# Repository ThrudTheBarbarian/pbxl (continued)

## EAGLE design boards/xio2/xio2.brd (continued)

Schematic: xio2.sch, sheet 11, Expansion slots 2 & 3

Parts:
C55, C56: 0.1uF; C0201
R63, R64: 10K; R0201
SLOT2, SLOT3: PCIE_64; PCI-E_64

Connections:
+3V3: SLOT2.A2, SLOT2.B5, SLOT2.B6, SLOT2.B7, SLOT3.A2, SLOT3.A3, SLOT3.B5, SLOT3.B6, SLOT3.B7; also elsewhere on the board
+5V: C55.1, C56.1, SLOT2.B1, SLOT2.B2, SLOT2.B3, SLOT3.B1, SLOT3.B2, SLOT3.B3; also elsewhere on the board
GND: C55.2, C56.2, R63.1, R64.1, SLOT2.A1, SLOT2.A3, SLOT2.A4, SLOT2.A5, SLOT2.A6, SLOT2.A7, SLOT3.A1, SLOT3.A4, SLOT3.A5, SLOT3.A6, SLOT3.A7; also elsewhere on the board
HOST_!EXTSEL!: SLOT2.B26, SLOT3.B26; also elsewhere on the board
HOST_!HALT!: SLOT2.B27, SLOT3.B27; also elsewhere on the board
HOST_!IRQ!: SLOT2.B28, SLOT3.B28; also elsewhere on the board
HOST_!MPD!: SLOT2.B29, SLOT3.B29; also elsewhere on the board
HOST_!REF!: SLOT2.B30, SLOT3.B30; also elsewhere on the board
HOST_!RST!: SLOT2.B31, SLOT3.B31; also elsewhere on the board
HOST_A0: SLOT2.A8, SLOT3.A8; also elsewhere on the board
HOST_A1: SLOT2.A9, SLOT3.A9; also elsewhere on the board
HOST_A2: SLOT2.A10, SLOT3.A10; also elsewhere on the board
HOST_A3: SLOT2.A11, SLOT3.A11; also elsewhere on the board
HOST_A4: SLOT2.A12, SLOT3.A12; also elsewhere on the board
HOST_A5: SLOT2.A13, SLOT3.A13; also elsewhere on the board
HOST_A6: SLOT2.A14, SLOT3.A14; also elsewhere on the board
HOST_A7: SLOT2.A15, SLOT3.A15; also elsewhere on the board
HOST_A8: SLOT2.A16, SLOT3.A16; also elsewhere on the board
HOST_A9: SLOT2.A17, SLOT3.A17; also elsewhere on the board
HOST_A10: SLOT2.A18, SLOT3.A18; also elsewhere on the board
HOST_A11: SLOT2.A19, SLOT3.A19; also elsewhere on the board
HOST_A12: SLOT2.A20, SLOT3.A20; also elsewhere on the board
HOST_A13: SLOT2.A21, SLOT3.A21; also elsewhere on the board
HOST_A14: SLOT2.A22, SLOT3.A22; also elsewhere on the board
HOST_A15: SLOT2.A23, SLOT3.A23; also elsewhere on the board
HOST_CLK: SLOT2.A24, SLOT3.A24; also elsewhere on the board
HOST_D0: SLOT2.A25, SLOT3.A25; also elsewhere on the board
HOST_D1: SLOT2.A26, SLOT3.A26; also elsewhere on the board
HOST_D2: SLOT2.A27, SLOT3.A27; also elsewhere on the board
HOST_D3: SLOT2.A28, SLOT3.A28; also elsewhere on the board
HOST_D4: SLOT2.A29, SLOT3.A29; also elsewhere on the board
HOST_D5: SLOT2.A30, SLOT3.A30; also elsewhere on the board
HOST_D6: SLOT2.A31, SLOT3.A31; also elsewhere on the board
HOST_D7: SLOT2.A32, SLOT3.A32; also elsewhere on the board
HOST_R/!W!: SLOT2.B32, SLOT3.B32; also elsewhere on the board
S2_PRESENT: R63.2, SLOT2.B4; also elsewhere on the board
S3_PRESENT: R64.2, SLOT3.B4; also elsewhere on the board
SBUS34_CTL0: SLOT2.B8, SLOT3.B8
SBUS34_CTL1: SLOT2.B9, SLOT3.B9
SBUS34_CTL2: SLOT2.B10, SLOT3.B10
SBUS34_CTL3: SLOT2.B11, SLOT3.B11
SBUS34_CTL4: SLOT2.B12, SLOT3.B12
SBUS34_D0: SLOT2.B18, SLOT3.B18
SBUS34_D1: SLOT2.B19, SLOT3.B19
SBUS34_D2: SLOT2.B20, SLOT3.B20
SBUS34_D3: SLOT2.B21, SLOT3.B21
SBUS34_D4: SLOT2.B22, SLOT3.B22
SBUS34_D5: SLOT2.B23, SLOT3.B23
SBUS34_D6: SLOT2.B24, SLOT3.B24
SBUS34_D7: SLOT2.B25, SLOT3.B25
SPI_CLK: SLOT2.B17, SLOT3.B17; also elsewhere on the board
SPI_IRQ2: SLOT2.B14; also elsewhere on the board
SPI_IRQ3: SLOT3.B14; also elsewhere on the board
SPI_MISO: SLOT2.B16, SLOT3.B16; also elsewhere on the board
SPI_MOSI: SLOT2.B15, SLOT3.B15; also elsewhere on the board
SPI_SS2: SLOT2.B13; also elsewhere on the board
SPI_SS3: SLOT3.B13; also elsewhere on the board

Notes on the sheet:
Slots 2,3
Slot id: 0,1,0
Slot id: 0,1,1
B1,2,3 B5,6,7 B4 A1,2,3 A4,5,6,7
+5V Slot 3.3v Card-present Slot ID GND

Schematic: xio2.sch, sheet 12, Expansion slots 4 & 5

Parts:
C81: 0.1uF; C0201
R65: 10K; R0201
SLOT4: PCIE_64; PCI-E_64

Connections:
+3V3: SLOT4.A1, SLOT4.B5, SLOT4.B6, SLOT4.B7; also elsewhere on the board
+5V: C81.1, SLOT4.B1, SLOT4.B2, SLOT4.B3; also elsewhere on the board
GND: C81.2, R65.1, SLOT4.A2, SLOT4.A3, SLOT4.A4, SLOT4.A5, SLOT4.A6, SLOT4.B8, SLOT4.B9, SLOT4.B10, SLOT4.B11, SLOT4.B12, SLOT4.B18, SLOT4.B19, SLOT4.B20, SLOT4.B21, SLOT4.B22, SLOT4.B23, SLOT4.B24, SLOT4.B25; also elsewhere on the board
HOST_!EXTSEL!: SLOT4.B26; also elsewhere on the board
HOST_!HALT!: SLOT4.B27; also elsewhere on the board
HOST_!IRQ!: SLOT4.B28; also elsewhere on the board
HOST_!MPD!: SLOT4.B29; also elsewhere on the board
HOST_!REF!: SLOT4.B30; also elsewhere on the board
HOST_!RST!: SLOT4.B31; also elsewhere on the board
HOST_A0: SLOT4.A7; also elsewhere on the board
HOST_A1: SLOT4.A8; also elsewhere on the board
HOST_A2: SLOT4.A9; also elsewhere on the board
HOST_A3: SLOT4.A10; also elsewhere on the board
HOST_A4: SLOT4.A11; also elsewhere on the board
HOST_A5: SLOT4.A12; also elsewhere on the board
HOST_A6: SLOT4.A13; also elsewhere on the board
HOST_A7: SLOT4.A14; also elsewhere on the board
HOST_A8: SLOT4.A15; also elsewhere on the board
HOST_A9: SLOT4.A16; also elsewhere on the board
HOST_A10: SLOT4.A17; also elsewhere on the board
HOST_A11: SLOT4.A18; also elsewhere on the board
HOST_A12: SLOT4.A19; also elsewhere on the board
HOST_A13: SLOT4.A20; also elsewhere on the board
HOST_A14: SLOT4.A21; also elsewhere on the board
HOST_A15: SLOT4.A22; also elsewhere on the board
HOST_CLK: SLOT4.A23; also elsewhere on the board
HOST_D0: SLOT4.A24; also elsewhere on the board
HOST_D1: SLOT4.A25; also elsewhere on the board
HOST_D2: SLOT4.A26; also elsewhere on the board
HOST_D3: SLOT4.A27; also elsewhere on the board
HOST_D4: SLOT4.A28; also elsewhere on the board
HOST_D5: SLOT4.A29; also elsewhere on the board
HOST_D6: SLOT4.A30; also elsewhere on the board
HOST_D7: SLOT4.A31; also elsewhere on the board
HOST_R/!W!: SLOT4.B32; also elsewhere on the board
S4_PRESENT: R65.2, SLOT4.B4; also elsewhere on the board
SPI_CLK: SLOT4.B17; also elsewhere on the board
SPI_IRQ4: SLOT4.B14; also elsewhere on the board
SPI_MISO: SLOT4.B16; also elsewhere on the board
SPI_MOSI: SLOT4.B15; also elsewhere on the board
SPI_SS4: SLOT4.B13; also elsewhere on the board

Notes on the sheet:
Slot 4
Slot id: 1,0,0
B1,2,3 B5,6,7 B4 A1,2,3 A4,5,6,7
+5V Slot 3.3v Card-present Slot ID GND

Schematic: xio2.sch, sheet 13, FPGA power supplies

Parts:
C11, C139, C140, C141: 10uF; C0805
C12: 22uF; C2012
C109, C110: 22uF; C0805
C111: 0.01uF; C0402
C112: 3900pF; C0402
C142: 0.1uF; C0402
C143: 1.2nF; C0603
C144: 13pF; C0805
C145: 560pF; C0402
C146: 33uF; C0805
FPGA_1_0: TLV62095; QFN50P310X310X100-16
L1: 1.5uH; L5650M
L2: 2.2uH; RESC4137X200
L3: 470nH; L0603
PEXT_10, PEXT_18: PINHD-1X2; 1X02
PEXT_33: PINHD-2X2; 2X02
R56: 1M; R0402
R129: 499K; R0402
R130: 40.2K; R0402
R131: 160K; R0402
R133: 10.5R; R0402
R134: 48.7K; R0402
R135: 6.04K; R0805
R136: 12K; R0805
R137: 2.67K; R0402
R138: 64.9R; R0402
R139: 105K; R0201
VREG_18: TPS62087RLTR; RLT0007A
VREG_33: LM21212; HTSSOP20

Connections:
+3V3: C145.1, C146.1, L2.2, PEXT_33.1, PEXT_33.2, PEXT_33.3, PEXT_33.4, R136.1; also elsewhere on the board
+5V: C11.1, C109.1, C139.1, C140.1, C141.1, FPGA_1_0.3 (DEF), FPGA_1_0.10 (AVIN), FPGA_1_0.11 (PVIN), FPGA_1_0.12 (PVIN), FPGA_1_0.13 (EN), R56.2, R129.1, R133.2, R139.1, VREG_18.7 (VIN), VREG_33.5 (PVIN), VREG_33.6 (PVIN), VREG_33.7 (PVIN); also elsewhere on the board
GND: C11.2, C12.2, C109.2, C110.2, C112.2, C139.2, C140.2, C141.2, C142.2, C146.2, FPGA_1_0.6 (AGND), FPGA_1_0.14 (PGND), FPGA_1_0.15 (PGND), FPGA_1_0.PAD (AGND), R131.2, R134.1, R137.2, VREG_18.5 (GND), VREG_33.8 (PGND), VREG_33.9 (PGND), VREG_33.10 (PGND), VREG_33.20 (AGND), VREG_33.TAB (GND); also elsewhere on the board
unnamed: L3.1, VREG_18.6 (SW)
unnamed: C111.1, FPGA_1_0.7 (CP)
unnamed: C111.2, FPGA_1_0.8 (CN)
unnamed: FPGA_1_0.1 (SW), FPGA_1_0.2 (SW), L1.1
unnamed: C142.1, R133.1, VREG_33.4 (AVIN)
unnamed: FPGA_1_0.5 (FB), R130.2, R131.1
unnamed: R134.2, VREG_33.1 (FADJ)
unnamed: C112.1, FPGA_1_0.9 (SS)
unnamed: C143.1, C144.1, VREG_33.18 (COMP)
unnamed: C143.2, R135.2
unnamed: C144.2, R135.1, R136.2, R137.1, R138.2, VREG_33.19 (FB)
unnamed: C145.2, R138.1
PGOOD33: R139.2, VREG_33.17 (PGOOD)
PGOOD_10: FPGA_1_0.4 (PG), R129.2, VREG_18.1 (EN)
PGOOD_18: R56.1, VREG_18.2 (PG), VREG_33.3 (EN)
SW_OUT: L2.1, VREG_33.11 (SW), VREG_33.12 (SW), VREG_33.13 (SW), VREG_33.14 (SW), VREG_33.15 (SW), VREG_33.16 (SW)
VCCAUX: C12.1, L3.2, PEXT_18.1, PEXT_18.2, VREG_18.3 (NC), VREG_18.4 (VOS); also elsewhere on the board
VCCINT: C110.1, FPGA_1_0.16 (VOS), L1.2, PEXT_10.1, PEXT_10.2, R130.1; also elsewhere on the board

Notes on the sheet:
C139 C140 C141 C142 C143 C144 C145 C146 R133 R134 R135 R136 R137 R138 R139 L2
Recommended Parts
C11 C12 L3 R56
FPGA power supplies
VCCINT @ 1.0v
Power supply notes
Power sequence is 1.0v rail @ 2A, which enables the 1.8v rail @ 1A, which enables the 3.3v rail @ 1A Both 1.8v and 3.3v need no minimum load All regulators are stable with ceramic caps
R131 and R130 ought to be at least 1%, preferably 0.1% resistors
VCCAUX @ 1.8v
VCCIO @ 3.3v

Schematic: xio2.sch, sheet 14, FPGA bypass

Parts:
C30, C36, C47, C48, C49, C50, C51, C58, C83, C84, C85, C86, C104: 0.47uF; C0201
C52: 47uF; C0805
C59, C74, C75, C76, C78, C79, C82, C102: 4.7uF; C0402
C73, C77, C101: 100uF; C0805
XC7S25: XC7S25; BGA196C100P14X14_1500X1500X146

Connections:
+3V3: C47.1, C48.1, C49.1, C50.1, C76.1, C77.1, C78.1, C79.1, C82.1, C83.1, C84.1, C85.1, C86.1; also elsewhere on the board
GND: C30.2, C36.2, C47.2, C48.2, C49.2, C50.2, C51.2, C52.2, C58.2, C59.2, C73.2, C74.2, C75.2, C76.2, C77.2, C78.2, C79.2, C82.2, C83.2, C84.2, C85.2, C86.2, C101.2, C102.2, C104.2, XC7S25.A1 (GND), XC7S25.A6 (GND), XC7S25.A9 (GND), XC7S25.A11 (GND), XC7S25.A14 (GND), XC7S25.B4 (GND), XC7S25.B7 (GND), XC7S25.B9 (GND), XC7S25.C2 (GND), XC7S25.C6 (GND), XC7S25.C7 (GND), XC7S25.C8 (GND), XC7S25.C9 (GND), XC7S25.C13 (GND), XC7S25.D5 (GND), XC7S25.D7 (GND), XC7S25.D9 (GND), XC7S25.D11 (GND), XC7S25.E1 (GND), XC7S25.E3 (GND), XC7S25.E6 (GND), XC7S25.E8 (GND), XC7S25.E10 (GND), XC7S25.E14 (GND), XC7S25.F5 (GND), XC7S25.F7 (GND_ADC_0), XC7S25.F9 (GND), XC7S25.G3 (GND), XC7S25.G6 (GND), XC7S25.G8 (VP_0), XC7S25.G10 (GND), XC7S25.G12 (GND), XC7S25.H5 (GND), XC7S25.H7 (VN_0), XC7S25.H9 (GND), XC7S25.J6 (GND), XC7S25.J10 (GND), XC7S25.K1 (GND), XC7S25.K5 (GND), XC7S25.K7 (GND), XC7S25.K9 (GND), XC7S25.K14 (GND), XC7S25.L4 (GND), XC7S25.L6 (GND), XC7S25.L8 (GND), XC7S25.L10 (GND), XC7S25.L11 (GND), XC7S25.N3 (GND), XC7S25.N5 (GND), XC7S25.N9 (GND), XC7S25.N12 (GND), XC7S25.P1 (GND), XC7S25.P14 (GND); also elsewhere on the board
VCCAUX: C51.1, C52.1, C58.1, C59.1, XC7S25.F8 (VCC_ADC_0), XC7S25.F10 (VCCAUX), XC7S25.H10 (VCCAUX), XC7S25.K10 (VCCAUX), XC7S25.L9 (VCCAUX); also elsewhere on the board
VCCINT: C30.1, C36.1, C73.1, C74.1, C75.1, C101.1, C102.1, C104.1, XC7S25.D6 (VCCINT), XC7S25.D8 (VCCINT), XC7S25.E5 (VCCBRAM), XC7S25.E7 (VCCINT), XC7S25.E9 (VCCINT), XC7S25.F6 (VCCINT), XC7S25.G5 (VCCBRAM), XC7S25.G9 (VCCINT), XC7S25.H6 (VCCINT), XC7S25.J5 (VCCBRAM), XC7S25.J9 (VCCINT), XC7S25.K6 (VCCINT), XC7S25.K8 (VCCINT); also elsewhere on the board

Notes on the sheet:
VccAux bypass caps
VccInt bypass caps
VccO bank 14
Bypass cap number and capacitance taken from UG483
VccBram bypass caps
VccO bank 34
No need for second 100uF
100uF 47uF 4.7uF 0.47uF
: GRM21BR60J107ME15L (0805) : GRM21BR60J476ME15L (0805) : GRM155R60J475ME87D (0402) : GRM033R60J474KE90D (0201)
100uF caps can be placed anywhere others within 2 electrical inches of part
FPGA power
Xilinx-recommended (smaller parts)
XADC is not used

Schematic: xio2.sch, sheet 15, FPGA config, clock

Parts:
A_MUX: TS3A27518EPWR; TSSOP24
BOOT_MODE: 209-3MS; EDG-03
C25, C96: 0.1uF; C0201
C97: 1uF; C0201
FPGA_CFG: W25Q80DVSNIG; SOIC8_150MIL
FPGA_DONE: LTST-C191KFKT; CHIPLED_0603
FPGA_PROG: XILINX-JTAG; 332-14
R52, R60: 33R; R0201
R54, R55, R57: 2.4K; R0201
R66: 200R; R0201
R68: 100R; R0402
R69, R70, R71, R78, R79: 4.7K; R0201
R82, R83, R84, R85: 10K; R0201
R125, R126, R127: 47K; R0201
R128: 1K; R0201
RESET_S7: Tac-switch; TACTILE-PTH
XC7S25: XC7S25; BGA196C100P14X14_1500X1500X146

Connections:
+3V3: A_MUX.8 (VCC), A_MUX.16 (NO6), A_MUX.18 (NO5), C25.1, C96.1, C97.1, FPGA_CFG.8 (VCC), FPGA_PROG.2 (VREF), R54.2, R55.2, R57.2, R66.2, R69.2, R78.2, R79.2, R82.1, R83.1, R84.1, R85.1, R128.1, XC7S25.N6 (VCCO_0), XC7S25.N8 (VCCO_0); also elsewhere on the board
BOOT_M0: BOOT_MODE.1, R127.1, XC7S25.M7 (M0_0)
BOOT_M1: BOOT_MODE.2, R126.1, XC7S25.M8 (M1_0)
BOOT_M2: BOOT_MODE.3, R125.1, XC7S25.M9 (M2_0)
FLASH_CLK: A_MUX.2 (NC1), R52.2
FLASH_CS: A_MUX.21 (NC4), R57.1, XC7S25.C11 (IO_L6P_T0_FCS_B_14)
FLASH_D0: A_MUX.1 (NC2), R60.2
FLASH_D1: A_MUX.23 (NC3), XC7S25.B12 (IO_L1N_T0_D01_DIN_14)
FLASH_D2: A_MUX.19 (NC5), R55.1, XC7S25.D10 (IO_L2P_T0_D02_14)
FLASH_D3: A_MUX.22 (NC6), R54.1, XC7S25.C10 (IO_L2N_T0_D03_14)
GND: A_MUX.5 (GND), A_MUX.17 (NO4), C25.2, C96.2, C97.2, FPGA_CFG.4 (VSS), FPGA_DONE.C, FPGA_PROG.1 (GND), FPGA_PROG.3 (GND), FPGA_PROG.5 (GND), FPGA_PROG.7 (GND), FPGA_PROG.9 (GND), FPGA_PROG.11 (GND), FPGA_PROG.13 (GND), R70.2, R71.2, R125.2, R126.2, R127.2, RESET_S7.1, RESET_S7.2, XC7S25.J7 (DXN_0), XC7S25.J8 (DXP_0); also elsewhere on the board
unnamed: R60.1, XC7S25.B11 (IO_L1P_T0_D00_MOSI_14)
unnamed: A_MUX.4 (COM1), FPGA_CFG.6 (SCK)
unnamed: BOOT_MODE.4, BOOT_MODE.5, BOOT_MODE.6, R128.2
unnamed: R52.1, XC7S25.A8 (CCLK_0)
unnamed: R66.1, R68.2, XC7S25.P9 (DONE_0)
unnamed: FPGA_DONE.A, R68.1
unnamed: A_MUX.6 (COM2), FPGA_CFG.5 (MOSI)
unnamed: A_MUX.7 (COM3), FPGA_CFG.2 (MISO)
unnamed: A_MUX.9 (COM4), FPGA_CFG.1 (SSEL)
unnamed: A_MUX.10 (COM5), FPGA_CFG.3 (#WP/IO2)
unnamed: A_MUX.12 (COM6), FPGA_CFG.7 (#HOLD/IO3)
unnamed: R69.1, RESET_S7.3, RESET_S7.4, XC7S25.L7 (PROGRAM_B_0)
unnamed: R78.1, XC7S25.P8 (INIT_B_0)
unnamed: A_MUX.20 (!EN!), R70.1
unnamed: R79.1, XC7S25.N7 (CFGBVS_0)
SPI_CLK: A_MUX.11 (NO1); also elsewhere on the board
SPI_MISO: A_MUX.15 (NO3); also elsewhere on the board
SPI_MOSI: A_MUX.13 (NO2); also elsewhere on the board
SPI_MUX_IN: A_MUX.14 (IN2), A_MUX.24 (IN1), R71.1; also elsewhere on the board
TCK: FPGA_PROG.6 (SCK/CCLK/TCK), R83.2, XC7S25.A7 (TCK_0)
TDI: FPGA_PROG.10 (MOSI/DIN/TDI), R85.2, XC7S25.P7 (TDI_0)
TDO: FPGA_PROG.8 (MISO/DONE/TDO), R84.2, XC7S25.P6 (TDO_0)
TMS: FPGA_PROG.4 (SS/PROG/TMS), R82.2, XC7S25.M6 (TMS_0)
VCCAUX: XC7S25.B8 (VCC_BATT_0); also elsewhere on the board

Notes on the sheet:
Bank 0 / Flash Config
Trace thickness Prepreg thickness Trace width Prepreg dielectric Trace impedance
0.035 mm 0.12 mm 8 mil 4.4 50.2 ohms
FLASH_CLK impedance matching
Default (NC) is that the FPGA has control over the SPI flash. If the STM pulls SPI_MUX_IN high, it gains control
Pins 12,14 are NC
Temp Sense Diodes Not Used
Done goes high once configuration completes
MUX operation
Boot mode
JTAG mode: Set M[2:0] to 101 Master SPI : Set M[2:0] to 001
Pull-ups for the JTAG lines

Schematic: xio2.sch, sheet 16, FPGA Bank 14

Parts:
HOST_IO: PINHD-2X20/90; 2X20/90
J1: 12401598E4#2A; AMPHENOL_12401598E4#2A
R59, R81: 10K; R0201
R113, R114, R115, R116, R117, R118: 50R; R0201
XC7S25: XC7S25; BGA196C100P14X14_1500X1500X146

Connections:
+3V3: R59.1, R113.2, R114.2, R115.2, R116.2, R117.2, R118.2, XC7S25.G13 (VCCO_14), XC7S25.K13 (VCCO_14), XC7S25.N13 (VCCO_14); also elsewhere on the board
GND: HOST_IO.40, J1.A1 (GND), J1.A12 (GND), J1.B1 (GND), J1.B12 (GND), J1.SH1 (SHIELD), J1.SH2 (SHIELD), J1.SH3 (SHIELD), J1.SH4 (SHIELD), R81.2; also elsewhere on the board
HOST_!EXTSEL!: HOST_IO.35, XC7S25.J11 (IO_L17P_T2_D30_14); also elsewhere on the board
HOST_!HALT!: HOST_IO.37, XC7S25.J12 (IO_L17N_T2_D29_14); also elsewhere on the board
HOST_!IRQ!: HOST_IO.39, XC7S25.K11 (IO_L19P_T3_D26_14); also elsewhere on the board
HOST_!MPD!: HOST_IO.32, XC7S25.K12 (IO_L19N_T3_D25_VREF_14); also elsewhere on the board
HOST_!REF!: HOST_IO.34, XC7S25.M11 (IO_L20P_T3_D24_14); also elsewhere on the board
HOST_!RST!: HOST_IO.36, XC7S25.M12 (IO_L20N_T3_D23_14); also elsewhere on the board
HOST_A0: HOST_IO.1, R59.2, R81.1, XC7S25.B10 (IO_L3P_T0_DQS_PUDC_B_14); also elsewhere on the board
HOST_A1: HOST_IO.3, XC7S25.A10 (IO_L3N_T0_DQS_EMCCLK_14); also elsewhere on the board
HOST_A2: HOST_IO.5, XC7S25.A12 (IO_L4P_T0_D04_14); also elsewhere on the board
HOST_A3: HOST_IO.7, XC7S25.A13 (IO_L4N_T0_D05_14); also elsewhere on the board
HOST_A4: HOST_IO.9, XC7S25.B13 (IO_L5P_T0_D06_14); also elsewhere on the board
HOST_A5: HOST_IO.11, XC7S25.B14 (IO_L5N_T0_D07_14); also elsewhere on the board
HOST_A6: HOST_IO.13, XC7S25.C12 (IO_L6N_T0_D08_VREF_14); also elsewhere on the board
HOST_A7: HOST_IO.15, XC7S25.F12 (IO_L7P_T1_D09_14); also elsewhere on the board
HOST_A8: HOST_IO.17, XC7S25.E12 (IO_L7N_T1_D10_14); also elsewhere on the board
HOST_A9: HOST_IO.19, XC7S25.D12 (IO_L8P_T1_D11_14); also elsewhere on the board
HOST_A10: HOST_IO.21, XC7S25.D13 (IO_L8N_T1_D12_14); also elsewhere on the board
HOST_A11: HOST_IO.23, XC7S25.G14 (IO_L9P_T1_DQS_14); also elsewhere on the board
HOST_A12: HOST_IO.25, XC7S25.F14 (IO_L9N_T1_DQS_D13_14); also elsewhere on the board
HOST_A13: HOST_IO.27, XC7S25.F13 (IO_L10P_T1_D14_14); also elsewhere on the board
HOST_A14: HOST_IO.29, XC7S25.E13 (IO_L10N_T1_D15_14); also elsewhere on the board
HOST_A15: HOST_IO.31, XC7S25.D14 (IO_L11P_T1_SRCC_14); also elsewhere on the board
HOST_CLK: HOST_IO.33, XC7S25.E11 (IO_0_14); also elsewhere on the board
HOST_CTL0: HOST_IO.2, XC7S25.N10 (IO_L23P_T3_D19_14)
HOST_CTL1: HOST_IO.4, XC7S25.N11 (IO_L23N_T3_D18_14)
HOST_D0: HOST_IO.6, XC7S25.C14 (IO_L11N_T1_SRCC_14); also elsewhere on the board
HOST_D1: HOST_IO.8, XC7S25.G11 (IO_L12P_T1_MRCC_14); also elsewhere on the board
HOST_D2: HOST_IO.10, XC7S25.F11 (IO_L12N_T1_MRCC_14); also elsewhere on the board
HOST_D3: HOST_IO.12, XC7S25.H11 (IO_L13P_T2_MRCC_14); also elsewhere on the board
HOST_D4: HOST_IO.14, XC7S25.H12 (IO_L13N_T2_MRCC_14); also elsewhere on the board
HOST_D5: HOST_IO.16, XC7S25.M13 (IO_L15P_T2_DQS_RDWR_B_14); also elsewhere on the board
HOST_D6: HOST_IO.18, XC7S25.L12 (IO_L16P_T2_CSI_B_14); also elsewhere on the board
HOST_D7: HOST_IO.20, XC7S25.L13 (IO_L16N_T2_D31_14); also elsewhere on the board
HOST_DIR0: HOST_IO.22; also elsewhere on the board
HOST_DIR1: HOST_IO.24; also elsewhere on the board
HOST_DIR2: HOST_IO.26; also elsewhere on the board
HOST_DIR3: HOST_IO.28; also elsewhere on the board
HOST_DIR4: HOST_IO.30; also elsewhere on the board
HOST_R/!W!: HOST_IO.38, XC7S25.L14 (IO_L15N_T2_DQS_DOUT_CSO_B_14); also elsewhere on the board
LX_MISC: J1.A5 (CC1), XC7S25.M10 (IO_25_14)
LX_RC_N: J1.B11 (SSRXP1), XC7S25.P11 (IO_L24N_T3_D16_14)
LX_RC_P: J1.B10 (SSRXN1), XC7S25.P10 (IO_L24P_T3_D17_14)
LX_RD_N: J1.B2 (SSTXP2), XC7S25.H14 (IO_L14N_T2_SRCC_14)
LX_RD_P: J1.B3 (SSTXN2), XC7S25.H13 (IO_L14P_T2_SRCC_14)
LX_TC_N: J1.A7 (DN1), R113.1, XC7S25.M14 (IO_L21N_T3_DQS_D22_14)
LX_TC_P: J1.A6 (DP1), R114.1, XC7S25.N14 (IO_L21P_T3_DQS_14)
LX_TD0_N: J1.A3 (SSTXN1), R115.1, XC7S25.P13 (IO_L22N_T3_D20_14)
LX_TD0_P: J1.A2 (SSTXP1), R116.1, XC7S25.P12 (IO_L22P_T3_D21_14)
LX_TD1_N: J1.A10 (SSRXN2), R117.1, XC7S25.J14 (IO_L18N_T2_D27_14)
LX_TD1_P: J1.A11 (SSRXP2), R118.1, XC7S25.J13 (IO_L18P_T2_D28_14)

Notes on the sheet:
Trace thickness Prepreg thickness Trace width Inter-trace spacing Prepreg dielectric Differential impedance
0.035 mm 0.12 mm 10 mil 7 mil 4.4 90.5 ohms
USB3 connections
FPGA Bank 14
TMDS_33 signalling requires 50R pull-ups to 3.3v on all inputs. Labels {RX*,TX*} are from perspective of the host board, so need to add pull-ups to TX* lines on this board. Will dissipate 13.5mA,
Pull-up specification
PUDC (connected to HOST_A0) cannot be floating according to UG470 (p27). The host interface can drive plenty to overpower a 10k pull-up and it's a slow bus, so this ought to work ok.
PUDC control

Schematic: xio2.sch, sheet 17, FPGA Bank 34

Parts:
C35, C88, C100: 0.1uF; C0201
EXPANSION: PINHD-2X6; 2X06
EXP_POWER: PINHD-1X2; 1X02
MUX-HI: IDTQS3VH257; SO16
MUX-LO: IDTQS3VH257; SO16
OSC1: 50 MHz oscillator; OSC_3.2X2.5MM
R58: 1K; R0201
R73, R74, R75: 33R; R0201
XC7S25: XC7S25; BGA196C100P14X14_1500X1500X146

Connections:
!ADDR_VALID_READ!: XC7S25.D1 (IO_L11P_T1_SRCC_34); also elsewhere on the board
!ADDR_VALID_WRITE!: XC7S25.C1 (IO_L11N_T1_SRCC_34); also elsewhere on the board
!GEN_CCTL!: XC7S25.F4 (IO_L12N_T1_MRCC_34); also elsewhere on the board
!GEN_S4!: XC7S25.H3 (IO_L13N_T2_MRCC_34); also elsewhere on the board
!GEN_S5!: XC7S25.H2 (IO_L14P_T2_SRCC_34); also elsewhere on the board
!SPI_IRQ!: XC7S25.L2 (IO_L22N_T3_34); also elsewhere on the board
+3V3: C35.1, C88.1, C100.1, EXPANSION.1, EXP_POWER.1, MUX-HI.16 (VCC), MUX-LO.16 (VCC), OSC1.4 (VCC), R58.1, XC7S25.G2 (VCCO_34), XC7S25.K2 (VCCO_34), XC7S25.N2 (VCCO_34); also elsewhere on the board
CART_RD4: XC7S25.H1 (IO_L14N_T2_SRCC_34); also elsewhere on the board
CART_RD5: XC7S25.J2 (IO_L15P_T2_DQS_34); also elsewhere on the board
EXT_IO0: EXPANSION.8; also elsewhere on the board
EXT_IO1: EXPANSION.10; also elsewhere on the board
FPGA_EXT0: EXPANSION.2, XC7S25.K3 (IO_L16N_T2_34)
FPGA_EXT1: EXPANSION.3, XC7S25.J4 (IO_L17P_T2_34)
FPGA_EXT2: EXPANSION.4, XC7S25.J3 (IO_L17N_T2_34)
FPGA_EXT3: EXPANSION.5, XC7S25.M1 (IO_L18P_T2_34)
FPGA_EXT4: EXPANSION.6, XC7S25.L1 (IO_L18N_T2_34)
FPGA_EXT5: EXPANSION.7, XC7S25.M3 (IO_L19P_T3_34)
GND: C35.2, C88.2, C100.2, EXPANSION.9, EXPANSION.11, EXPANSION.12, EXP_POWER.2, MUX-HI.8 (GND), MUX-HI.15 (!E!), MUX-LO.8 (GND), MUX-LO.15 (!E!), OSC1.2 (GND); also elsewhere on the board
HOST_DIR0: XC7S25.B6 (IO_0_34); also elsewhere on the board
HOST_DIR1: XC7S25.D3 (IO_L1P_T0_34); also elsewhere on the board
HOST_DIR2: XC7S25.C3 (IO_L1N_T0_34); also elsewhere on the board
HOST_DIR3: XC7S25.A4 (IO_L2P_T0_34); also elsewhere on the board
HOST_DIR4: XC7S25.A3 (IO_L2N_T0_34); also elsewhere on the board
LX_CLK: OSC1.3 (OUT), XC7S25.G4 (IO_L12P_T1_MRCC_34)
unnamed: OSC1.1 (INH), R58.2
S7_DBG0: XC7S25.H4 (IO_L13P_T2_MRCC_34); also elsewhere on the board
S7_DBG1: XC7S25.J1 (IO_L15N_T2_DQS_34); also elsewhere on the board
S7_DBG2: XC7S25.K4 (IO_L16P_T2_34); also elsewhere on the board
SPI_IRQ0: XC7S25.L5 (IO_25_34); also elsewhere on the board
SPI_IRQ1: XC7S25.N4 (IO_L24N_T3_34); also elsewhere on the board
SPI_IRQ2: XC7S25.P5 (IO_L24P_T3_34); also elsewhere on the board
SPI_IRQ3: XC7S25.M4 (IO_L23N_T3_34); also elsewhere on the board
SPI_IRQ4: XC7S25.M5 (IO_L23P_T3_34); also elsewhere on the board
STMDATA_A0: MUX-LO.2 (A0), XC7S25.B3 (IO_L3P_T0_DQS_34)
STMDATA_A1: MUX-LO.5 (A1), XC7S25.A2 (IO_L3N_T0_DQS_34)
STMDATA_A2: MUX-LO.11 (A2), XC7S25.B5 (IO_L4P_T0_34)
STMDATA_A3: MUX-LO.14 (A3), XC7S25.A5 (IO_L4N_T0_34)
STMDATA_A4: MUX-HI.2 (A0), XC7S25.B2 (IO_L5P_T0_34)
STMDATA_A5: MUX-HI.5 (A1), XC7S25.B1 (IO_L5N_T0_34)
STMDATA_A6: MUX-HI.11 (A2), XC7S25.C5 (IO_L6P_T0_34)
STMDATA_A7: MUX-HI.14 (A3), XC7S25.C4 (IO_L6N_T0_VREF_34)
STMDATA_B0: MUX-LO.3 (B0), XC7S25.E4 (IO_L7P_T1_34)
STMDATA_B1: MUX-LO.6 (B1), XC7S25.D4 (IO_L7N_T1_34)
STMDATA_B2: MUX-LO.10 (B2), XC7S25.F3 (IO_L8P_T1_34)
STMDATA_B3: MUX-LO.13 (B3), XC7S25.F2 (IO_L8N_T1_34)
STMDATA_B4: MUX-HI.3 (B0), XC7S25.G1 (IO_L9P_T1_DQS_34)
STMDATA_B5: MUX-HI.6 (B1), XC7S25.F1 (IO_L9N_T1_DQS_34)
STMDATA_B6: MUX-HI.10 (B2), XC7S25.E2 (IO_L10P_T1_34)
STMDATA_B7: MUX-HI.13 (B3), XC7S25.D2 (IO_L10N_T1_34)
STM_MUX_CTL: MUX-HI.1 (S), MUX-LO.1 (S); also elsewhere on the board
STM_MUX_D0: MUX-LO.4 (Y0); also elsewhere on the board
STM_MUX_D1: MUX-LO.7 (Y1); also elsewhere on the board
STM_MUX_D2: MUX-LO.9 (Y2); also elsewhere on the board
STM_MUX_D3: MUX-LO.12 (Y3); also elsewhere on the board
STM_MUX_D4: MUX-HI.4 (Y0); also elsewhere on the board
STM_MUX_D5: MUX-HI.7 (Y1); also elsewhere on the board
STM_MUX_D6: MUX-HI.9 (Y2); also elsewhere on the board
STM_MUX_D7: MUX-HI.12 (Y3); also elsewhere on the board
XSPI5_MISO: XC7S25.P3 (IO_L21N_T3_DQS_34); also elsewhere on the board
XSPI5_MOSI: R74.1; also elsewhere on the board
XSPI5_MOSI_R: R74.2, XC7S25.L3 (IO_L22P_T3_34)
XSPI5_SCK: R75.1; also elsewhere on the board
XSPI5_SCK_R: R75.2, XC7S25.P4 (IO_L21P_T3_DQS_34)
XSPI6_MISO: R73.1; also elsewhere on the board
XSPI6_MISO_R: R73.2, XC7S25.P2 (IO_L20P_T3_34)
XSPI6_MOSI: XC7S25.N1 (IO_L20N_T3_34); also elsewhere on the board
XSPI6_SCK: XC7S25.M2 (IO_L19N_T3_VREF_34); also elsewhere on the board

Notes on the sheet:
STMDATA_A* is an input STMDATA_B* is an output STM controls whether to read or write data using STM_MUX_CTL in IRQ handler Mux removes need to sync FPGA & STM
SPI5 to be used with FPGA as master. SPI6 to be used with STM as master Resistors sited close to source signal
SPI termination
HOST_DIR0 : HOST_DIR1 : HOST_DIR2 : HOST_DIR3 : HOST_DIR4 :
Direction control
Host data bus Host address bus Host R/!W! signal Host !REF! signal Host !HALT! signal
STM32 data bus
Bypass caps for muxes
FPGA Bank 34
This is for a more stable board mount

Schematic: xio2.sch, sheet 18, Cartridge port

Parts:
C57, C60, C61, C62, C63, C64, C65, C66, C67, C68, C69, C70, C71, C72: 0.1uF; C0201
CARTRIDGE: 5650118-1; A8_CART
LVL_AHI: SN74LVC8T245; TSSOP24
LVL_ALO: SN74LVC8T245; TSSOP24
LVL_D: SN74LVC8T245; TSSOP24
U$5, U$6, U$7, U$8: 74LVC1T45GWSOT866; SOT886

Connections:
!GEN_CCTL!: LVL_AHI.8 (A6); also elsewhere on the board
!GEN_S4!: LVL_AHI.9 (A7); also elsewhere on the board
!GEN_S5!: LVL_AHI.10 (A8); also elsewhere on the board
+3V3: C57.1, C60.1, C61.1, C62.1, C63.1, C64.1, C65.1, LVL_AHI.1 (VCCA), LVL_AHI.2 (DIR), LVL_ALO.1 (VCCA), LVL_ALO.2 (DIR), LVL_D.1 (VCCA), U$5.1 (VCCA), U$5.5 (DIR), U$6.1 (VCCA), U$6.5 (DIR), U$7.6 (VCCB), U$8.6 (VCCB); also elsewhere on the board
+5V: C66.1, C67.1, C68.1, C69.1, C70.1, C71.1, C72.1, CARTRIDGE.P13 (VCC5), LVL_AHI.23 (VCCB), LVL_AHI.24 (VCCB), LVL_ALO.23 (VCCB), LVL_ALO.24 (VCCB), LVL_D.23 (VCCB), LVL_D.24 (VCCB), U$5.6 (VCCB), U$6.6 (VCCB), U$7.1 (VCCA), U$7.5 (DIR), U$8.1 (VCCA), U$8.5 (DIR); also elsewhere on the board
CART_!CCTL!: CARTRIDGE.P15 (!CCTL!), LVL_AHI.16 (B6)
CART_!S4!: CARTRIDGE.P1 (!S4!), LVL_AHI.15 (B7)
CART_!S5!: CARTRIDGE.P12 (!S5!), LVL_AHI.14 (B8)
CART_A0: CARTRIDGE.P5 (A0), LVL_ALO.21 (B1)
CART_A1: CARTRIDGE.P4 (A1), LVL_ALO.20 (B2)
CART_A2: CARTRIDGE.P3 (A2), LVL_ALO.19 (B3)
CART_A3: CARTRIDGE.P2 (A3), LVL_ALO.18 (B4)
CART_A4: CARTRIDGE.PC (A4), LVL_ALO.17 (B5)
CART_A5: CARTRIDGE.PD (A5), LVL_ALO.16 (B6)
CART_A6: CARTRIDGE.PE (A6), LVL_ALO.15 (B7)
CART_A7: CARTRIDGE.PF (A7), LVL_ALO.14 (B8)
CART_A8: CARTRIDGE.PH (A8), LVL_AHI.21 (B1)
CART_A9: CARTRIDGE.PJ (A9), LVL_AHI.20 (B2)
CART_A10: CARTRIDGE.PP (A10), LVL_AHI.19 (B3)
CART_A11: CARTRIDGE.PN (A11), LVL_AHI.18 (B4)
CART_A12: CARTRIDGE.PK (A12), LVL_AHI.17 (B5)
CART_CLK: CARTRIDGE.PS (B02), U$5.4 (B)
CART_D0: CARTRIDGE.P10 (D0), LVL_D.21 (B1)
CART_D1: CARTRIDGE.P9 (D1), LVL_D.20 (B2)
CART_D2: CARTRIDGE.P8 (D2), LVL_D.19 (B3)
CART_D3: CARTRIDGE.PL (D3), LVL_D.18 (B4)
CART_D4: CARTRIDGE.P6 (D4), LVL_D.17 (B5)
CART_D5: CARTRIDGE.P7 (D5), LVL_D.16 (B6)
CART_D6: CARTRIDGE.P11 (D6), LVL_D.15 (B7)
CART_D7: CARTRIDGE.PM (D7), LVL_D.14 (B8)
CART_R/!W!: CARTRIDGE.PR (R/!W!), U$6.4 (B)
CART_RD4: U$7.4 (B); also elsewhere on the board
CART_RD5: U$8.4 (B); also elsewhere on the board
GND: C57.2, C60.2, C61.2, C62.2, C63.2, C64.2, C65.2, C66.2, C67.2, C68.2, C69.2, C70.2, C71.2, C72.2, CARTRIDGE.PB (GND), LVL_AHI.11 (GND), LVL_AHI.12 (GND), LVL_AHI.13 (GND), LVL_AHI.22 (!OE!), LVL_ALO.11 (GND), LVL_ALO.12 (GND), LVL_ALO.13 (GND), LVL_ALO.22 (!OE!), LVL_D.11 (GND), LVL_D.12 (GND), LVL_D.13 (GND), LVL_D.22 (!OE!), U$5.2 (GND), U$6.2 (GND), U$7.2 (GND), U$8.2 (GND); also elsewhere on the board
HOST_A0: LVL_ALO.3 (A1); also elsewhere on the board
HOST_A1: LVL_ALO.4 (A2); also elsewhere on the board
HOST_A2: LVL_ALO.5 (A3); also elsewhere on the board
HOST_A3: LVL_ALO.6 (A4); also elsewhere on the board
HOST_A4: LVL_ALO.7 (A5); also elsewhere on the board
HOST_A5: LVL_ALO.8 (A6); also elsewhere on the board
HOST_A6: LVL_ALO.9 (A7); also elsewhere on the board
HOST_A7: LVL_ALO.10 (A8); also elsewhere on the board
HOST_A8: LVL_AHI.3 (A1); also elsewhere on the board
HOST_A9: LVL_AHI.4 (A2); also elsewhere on the board
HOST_A10: LVL_AHI.5 (A3); also elsewhere on the board
HOST_A11: LVL_AHI.6 (A4); also elsewhere on the board
HOST_A12: LVL_AHI.7 (A5); also elsewhere on the board
HOST_CLK: U$5.3 (A); also elsewhere on the board
HOST_D0: LVL_D.3 (A1); also elsewhere on the board
HOST_D1: LVL_D.4 (A2); also elsewhere on the board
HOST_D2: LVL_D.5 (A3); also elsewhere on the board
HOST_D3: LVL_D.6 (A4); also elsewhere on the board
HOST_D4: LVL_D.7 (A5); also elsewhere on the board
HOST_D5: LVL_D.8 (A6); also elsewhere on the board
HOST_D6: LVL_D.9 (A7); also elsewhere on the board
HOST_D7: LVL_D.10 (A8); also elsewhere on the board
HOST_DIR0: LVL_D.2 (DIR); also elsewhere on the board
HOST_R/!W!: U$6.3 (A); also elsewhere on the board
unnamed: CARTRIDGE.PA (RD4), U$7.3 (A)
unnamed: CARTRIDGE.P14 (RD5), U$8.3 (A)

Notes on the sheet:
Dir=high : A->B tPD_AB : 0.7 .. 4.4ns tPD_BA : 0.6 .. 5.4ns
74LVCH1T45GW:
SN74LVC8T245:
Dir=high : A->B tPD_AB : 0.5 .. 4.4ns tPD_BA : 0.6 .. 6ns
HOST_DIR0 :
Direction control / timings
Host data bus
Cartridge support

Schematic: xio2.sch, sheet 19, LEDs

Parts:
LD_0ACT, LD_1ACT, LD_2ACT, LD_3ACT, LD_4ACT: LTST-C191KRKT; CHIPLED_0603
LD_0P, LD_1P, LD_2P, LD_3P, LD_4P: SML-D12D1WT86; CHIPLED_0603
LD_7DBG0, LD_7DBG1, LD_7DBG2: IN-S63BTA; CHIPLED_0603
LD_AUX: LTST-S270GKT; CHIPLED_0603
LD_INT: LTST-S270GKT; CHIPLED_0603
LD_V33: LTST-S270GKT; CHIPLED_0603
Q3, Q4: BC817-16LT3G; SOT23-R
R67, R77: 150R; R0402
R76, R80: 330R; R0402
R87, R98, R101, R104, R107, R112: 59R; R0402
R94, R99, R102, R105, R108, R109, R110, R111: 130R; R0402

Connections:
+3V3: R112.1; also elsewhere on the board
+5V: R67.1, R77.1; also elsewhere on the board
GND: LD_0ACT.C, LD_0P.C, LD_1ACT.C, LD_1P.C, LD_2ACT.C, LD_2P.C, LD_3ACT.C, LD_3P.C, LD_4ACT.C, LD_4P.C, LD_7DBG0.C, LD_7DBG1.C, LD_7DBG2.C, LD_V33.C, Q3.2 (E), Q4.2 (E); also elsewhere on the board
unnamed: LD_INT.A, R67.2
unnamed: Q3.1 (B), R76.1
unnamed: LD_INT.C, Q3.3 (C)
unnamed: LD_AUX.A, R77.2
unnamed: LD_0P.A, R87.2
unnamed: LD_0ACT.A, R94.2
unnamed: Q4.1 (B), R80.1
unnamed: LD_AUX.C, Q4.3 (C)
unnamed: LD_1P.A, R98.2
unnamed: LD_1ACT.A, R99.2
unnamed: LD_2P.A, R101.2
unnamed: LD_2ACT.A, R102.2
unnamed: LD_3P.A, R104.2
unnamed: LD_3ACT.A, R105.2
unnamed: LD_4P.A, R107.2
unnamed: LD_4ACT.A, R108.2
unnamed: LD_7DBG0.A, R109.2
unnamed: LD_7DBG1.A, R110.2
unnamed: LD_7DBG2.A, R111.2
unnamed: LD_V33.A, R112.2
S0_PRESENT: R87.1; also elsewhere on the board
S1_PRESENT: R98.1; also elsewhere on the board
S2_PRESENT: R101.1; also elsewhere on the board
S3_PRESENT: R104.1; also elsewhere on the board
S4_PRESENT: R107.1; also elsewhere on the board
S7_DBG0: R109.1; also elsewhere on the board
S7_DBG1: R110.1; also elsewhere on the board
S7_DBG2: R111.1; also elsewhere on the board
SPI_SS0: R94.1; also elsewhere on the board
SPI_SS1: R99.1; also elsewhere on the board
SPI_SS2: R102.1; also elsewhere on the board
SPI_SS3: R105.1; also elsewhere on the board
SPI_SS4: R108.1; also elsewhere on the board
VCCAUX: R80.2; also elsewhere on the board
VCCINT: R76.2; also elsewhere on the board

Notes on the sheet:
Debugging LEDs
Green LED
Amber LED
Orange LED
Red LED
Green and Orange LEDs are configured for 20mA current
Amber and Red LEDs are configured for 10mA current
LED resistor values

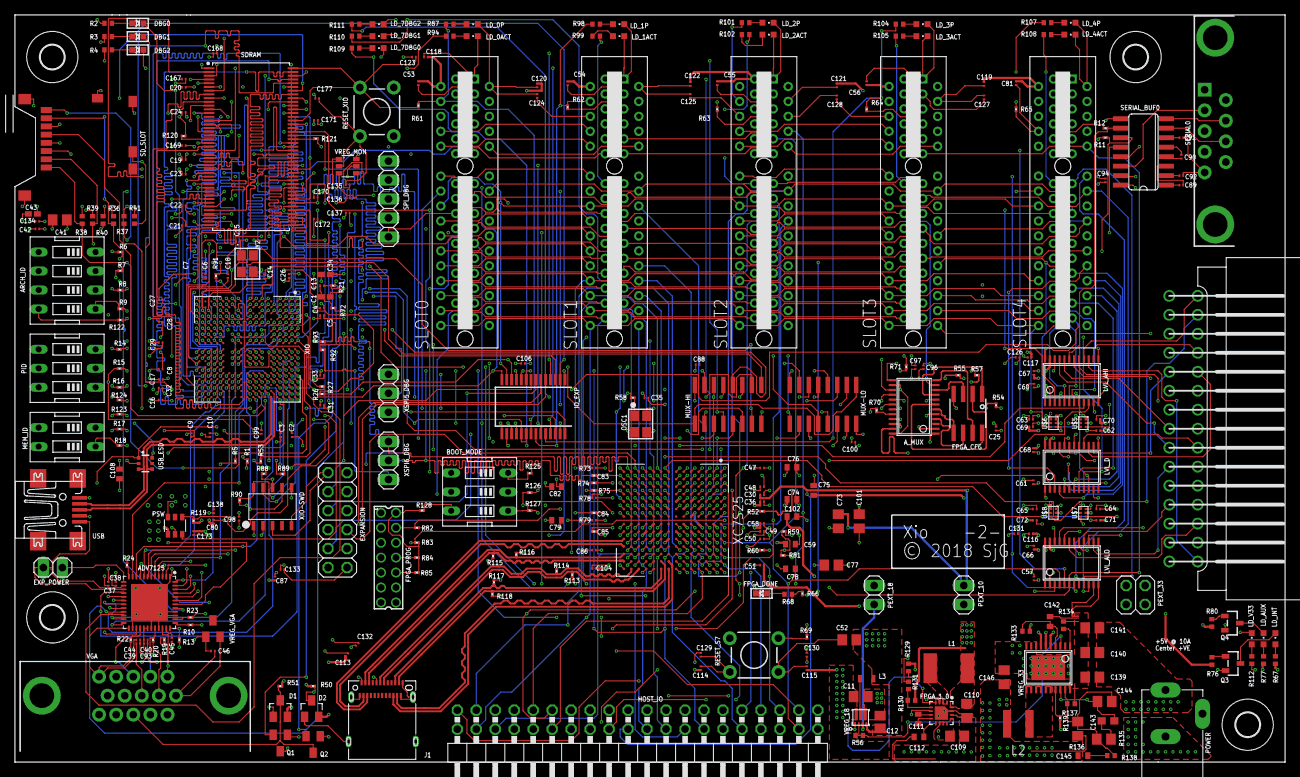
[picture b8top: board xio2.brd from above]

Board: 6 copper layers, 170.0 x 100.0 mm, 352 parts (0 on the bottom side), 410 nets.
